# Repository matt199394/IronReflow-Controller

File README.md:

Iron Relow station Aka Soldering/Desoldering SMD Station

Brilliant project find on youtube at https://www.youtube.com/watch?v=2hhL1sXg254&t=1831s
I have made my custom PCB. 
You have to set some #DEFINE to set the heater time and fine tuning the proper temperature. You have to do some trial depending of solder paste and of iron plate caracteristics.
In my case I have use a chaep heating plate and 138°C lead free paste.
Works very well and I'm pretty ststisfied!
Thanks to Davide Gatti for the video and code!
Video demo: https://www.youtube.com/watch?v=i8gFOUQswV8

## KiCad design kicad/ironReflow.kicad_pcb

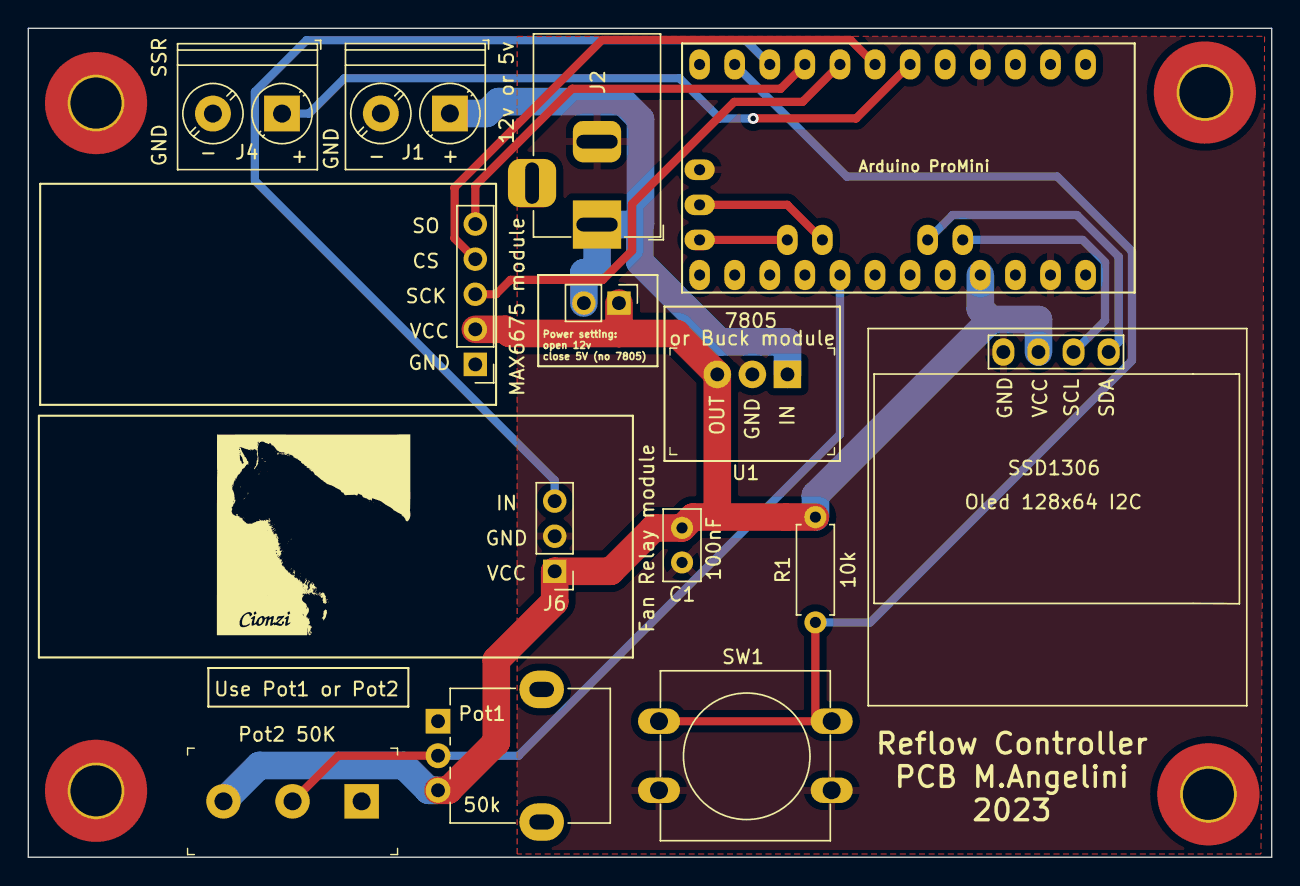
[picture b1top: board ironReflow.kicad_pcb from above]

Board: 2 copper layers, 90.0 x 60.0 mm, 19 parts (0 on the bottom side), 12 nets.

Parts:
 : LOGO; cionzi
Arduino ProMini: ArduinoProMini; pro_mini
C1: 100nF; C_Disc_D5.0mm_W2.5mm_P2.50mm
H1, H2, H3, H4: MountingHole; MountingHole_3.7mm_Pad_TopBottom
J1: 12v or 5v; TerminalBlock_Phoenix_PT-1,5-2-5.0-H_1x02_P5.00mm_Horizontal
J2: Conn_Coaxial_Power; BarrelJack_Horizontal
J3: Conn_01x02_Male; PinHeader_1x02_P2.54mm_Vertical
J4: SSR; TerminalBlock_Phoenix_PT-1,5-2-5.0-H_1x02_P5.00mm_Horizontal
J5: MAX6675 module; PinHeader_1x05_P2.54mm_Vertical
J6: Fan Relay module; PinHeader_1x03_P2.54mm_Vertical
J7: Pot2 50K; Term_Block_1x3_P5mm
Oled 128x64 I2C: SSD1306; 128x64OLED_I2C
Pot1: 50k; Potentiometer_Alpha_RD901F-40-00D_Single_Vertical
R1: 10k; R_Axial_DIN0207_L6.3mm_D2.5mm_P7.62mm_Horizontal
SW1: SW_Push; SW_PUSH-12mm
U1: 7805; 3-SIP_Module_V7805-500

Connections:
+5V: Arduino ProMini.21 (VCC), C1.1, J3.1, J5.2, J6.1, J7.3, Oled 128x64 I2C.2 (VCC), Pot1.3, R1.2, U1.3 (Vo+)
+12V: J1.1, J2.1 (In), J3.2, U1.1 (Vin+)
GND: Arduino ProMini.4 (GND), Arduino ProMini.23 (GND), Arduino ProMini.29 (GND), C1.2, J1.2, J2.2 (Ext), J4.2, J5.1, J6.2, J7.1, Oled 128x64 I2C.1 (GND), Pot1.1, SW1.2, U1.2 (GND)
unnamed: Arduino ProMini.26 ((PCINT13/SCL/ADC5)PC5/19/A5), Oled 128x64 I2C.3 (SCL)
unnamed: Arduino ProMini.25 ((PCINT12/SDA/ADC4)PC4/18/A4), Oled 128x64 I2C.4 (SDA)
unnamed: Arduino ProMini.6 ((PCINT19/OC2B/INT1/PWM)PD3/3), J4.1
unnamed: Arduino ProMini.7 ((PCINT20/XCK/T0)PD4/4), J5.4
unnamed: Arduino ProMini.8 ((PCINT21/OC0B/T1/PWM)PD5/5), J5.3
unnamed: Arduino ProMini.9 ((PCINT22/OC0A/AIN0/PWM)PD6/6), J5.5
unnamed: Arduino ProMini.10 ((PCINT23/AIN1)PD7/7), J6.3
unnamed: Arduino ProMini.11 ((PCINT0/CLKO/ICP1)PB0/8), R1.1, SW1.1
unnamed: Arduino ProMini.17 ((PCINT8/ADC0)PC0/14/A0), J7.2, Pot1.2
